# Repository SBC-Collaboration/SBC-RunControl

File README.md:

#  SBC-RunControl

Data acquisition software for the Scintillating Bubble Chamber experiment. For more details, please use the documentation linked below.

## [Documentation](https://runcontrol.readthedocs.io)
- [Usage](https://runcontrol.readthedocs.io/stable/usage.html)
- [Project Description](https://runcontrol.readthedocs.io/stable/project_description.html)
- [Data Formats](https://runcontrol.readthedocs.io/stable/data_format.html)
- [Documentation](https://runcontrol.readthedocs.io/stable/documentation.html)
- [Git workflow and guidelines](https://runcontrol.readthedocs.io/stable/git_workflow.html)
- [API](https://runcontrol.readthedocs.io/stable/api.html)
- [Changelog](https://runcontrol.readthedocs.io/stable/changelog.html)

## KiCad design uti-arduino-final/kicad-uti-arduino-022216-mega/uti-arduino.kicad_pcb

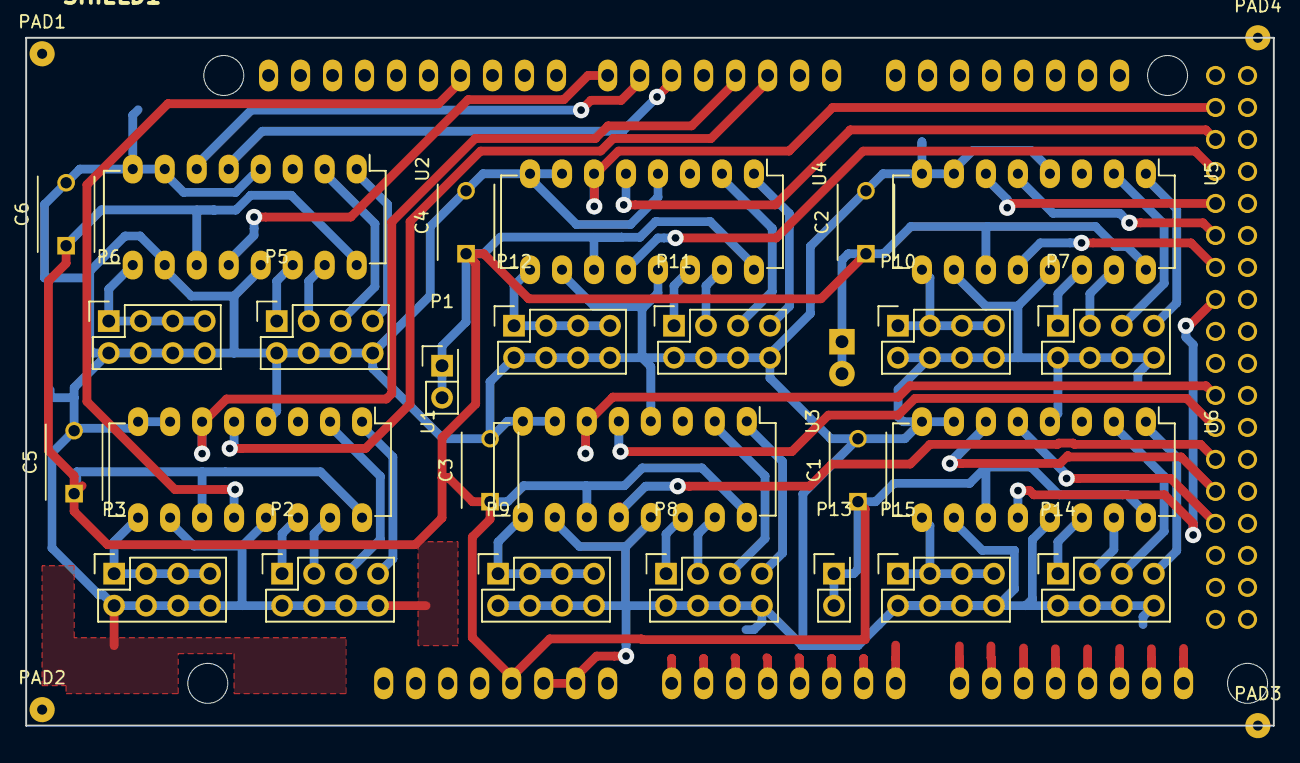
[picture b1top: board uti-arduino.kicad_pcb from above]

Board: 2 copper layers, 99.1 x 54.6 mm, 32 parts (1 on the bottom side), 50 nets.

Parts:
C1, C2, C3, C4, C5, C6: 100n; C_Disc_D6_P5
P1, P13: CONN_01X02; Socket_Strip_Straight_2x01
P2, P3, P5, P6, P7, P8, P9, P10, P11, P12, P14, P15: CONN_02X04; Socket_Strip_Straight_2x04
P4: CONN_01X02; Socket_Strip_Straight_1x02
PAD1: Pad1; SolderWirePad_single_0-8mmDrill
PAD2: Pad2; SolderWirePad_single_0-8mmDrill
PAD3: Pad3; SolderWirePad_single_0-8mmDrill
PAD4: Pad4; SolderWirePad_single_0-8mmDrill
SHIELD1: ARDUINO_SHIELD; ARDUINO_MEGA_SHIELD
U1, U2, U3, U4, U5, U6: UTI; DIP-16_W7.62mm_LongPads

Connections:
+5V: C1.1, C2.1, C3.1, C4.1, C5.1, C6.1, P1.1, P1.2, P4.1, P4.2, P13.1, P13.2, SHIELD1.5V, U1.11, U1.16, U2.11, U2.16, U3.11, U3.16, U4.11, U4.16, U5.11, U5.16, U6.11, U6.16
GND: C1.2, C2.2, C3.2, C4.2, C5.2, C6.2, P2.2, P2.4, P2.6, P2.8, P3.2, P3.4, P3.6, P3.8, P5.2, P5.4, P5.6, P5.8, P6.2, P6.4, P6.6, P6.8, P7.2, P7.4, P7.6, P7.8, P8.2, P8.4, P8.6, P8.8, P9.2, P9.4, P9.6, P9.8, P10.2, P10.4, P10.6, P10.8, P11.2, P11.4, P11.6, P11.8, P12.2, P12.4, P12.6, P12.8, P14.2, P14.4, P14.6, P14.8, P15.2, P15.4, P15.6, P15.8, SHIELD1.GND1, SHIELD1.GND2, U1.4, U1.7, U1.8, U1.10, U1.13, U2.4, U2.7, U2.8, U2.10, U2.13, U3.4, U3.7, U3.8, U3.10, U3.13, U4.4, U4.7, U4.8, U4.10, U4.13, U5.4, U5.7, U5.8, U5.10, U5.13, U6.4, U6.7, U6.8, U6.10, U6.13
unnamed: P2.1, U1.14
unnamed: P2.3, U1.15
unnamed: P2.5, U1.2
unnamed: P2.7, U1.1
unnamed: P3.1, P3.3, P3.5, P3.7, U1.9
unnamed: P5.1, U2.14
unnamed: P5.3, U2.15
unnamed: P5.5, U2.2
unnamed: P5.7, U2.1
unnamed: P6.1, P6.3, P6.5, P6.7, U2.9
unnamed: P7.1, U5.14
unnamed: P7.3, U5.15
unnamed: P7.5, U5.2
unnamed: P7.7, U5.1
unnamed: P8.1, U3.14
unnamed: P8.3, U3.15
unnamed: P8.5, U3.2
unnamed: P8.7, U3.1
unnamed: P9.1, P9.3, P9.5, P9.7, U3.9
unnamed: P10.1, P10.3, P10.5, P10.7, U5.9
unnamed: P11.1, U4.14
unnamed: P11.3, U4.15
unnamed: P11.5, U4.2
unnamed: P11.7, U4.1
unnamed: P12.1, P12.3, P12.5, P12.7, U4.9
unnamed: P14.1, U6.14
unnamed: P14.3, U6.15
unnamed: P14.5, U6.2
unnamed: P14.7, U6.1
unnamed: P15.1, P15.3, P15.5, P15.7, U6.9
unnamed: SHIELD1.2, U1.5
unnamed: SHIELD1.3, U1.6
unnamed: SHIELD1.5, U2.5
unnamed: SHIELD1.6, U2.6
unnamed: SHIELD1.7, U2.12
unnamed: SHIELD1.11, U1.12
unnamed: SHIELD1.22, U4.6
unnamed: SHIELD1.24, U4.5
unnamed: SHIELD1.26, U4.12
unnamed: SHIELD1.28, U5.6
unnamed: SHIELD1.30, U5.5
unnamed: SHIELD1.32, U5.12
unnamed: SHIELD1.34, U6.12
unnamed: SHIELD1.40, U3.6
unnamed: SHIELD1.42, U3.5
unnamed: SHIELD1.44, U3.12
unnamed: SHIELD1.46, U6.6
unnamed: SHIELD1.48, U6.5

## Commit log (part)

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2025-02-11 Add a new CAEN page. Add more configs
2025-02-11 Change config module to match settings page
2025-02-12 Add CAEN group range setting
2025-02-12 Change some of the config and UI code to work with UI changes
2025-02-12 Save CAEN data dicts in a list and write at the end
2025-02-12 Add trigger counting mode box
2025-02-13 Move RedDigitizerPlusPlus install from local to pip
2025-02-14 Change some variable names to match CAEN driver and UI
2025-02-17 Use enabled channels and record length from CAEN to set writer, since rec_length can only be multiples of 3
2025-02-18 Remove json wave names to reduce length, also print gates in Arduino serial
2025-02-18 reset niusb device at starting run
2025-02-18 Stop saving wave name in clock arduino json
2025-02-18 Revert to default tab
2025-02-20 Update CAEN plot on main page
2025-02-20 Change event info binary file to have string as trigger source
2025-02-20 Make clock arduino run faster With LED gate and all 16 channels, now the clock arduino can complete a loop in 100us. Changes made include: 1. Simplify the logic for checking time at the end 2. Only m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
2025-02-24 Add CAEN enable in config, change number of modules that need to be ready at each stage
2025-02-24 Add loop time in arduino json
2025-02-24 Minor changes
2025-02-25 Add enable field for acoustics module
2025-02-25 Now acoustics module can be disabled, and also writes the ini file
2025-02-25 Edit more of the buddies in Pyside6 designer
2025-02-26 Rename seg count boxes
2025-02-26 Implement acousitcs settings in config module
2025-02-26 Fix acoustics ini file generation to match GaGe's requirements
2025-02-26 Remove acoustics channel enable checkbox
2025-02-27 Clean up unused imports
2025-03-04 Change unit of acoustics dc offset
2025-03-04 RC now saves acoustic channel DC offset in .ini file
2025-03-04 Add acous channel name saving/loading
2025-03-05 Deal with case when wave is wrapped, i.e. (duty+phase)>period. Also remove state to make it faster. A loop completes in ~60us now.
2025-03-05 Set LED inhibit pin on trigger arduino to be output. Otherwise it'll always be high
2025-03-05 Add sipm amp3 status light
2025-03-09 Consolidate project structure into project description, also update configuration file definition
2025-03-09 Add definition for CAEN and GaGe data
2025-03-09 Update project structure, and chapter hierachy
2025-03-10 Update dependencies docs
2025-03-10 Move info from main README to docs
2025-03-11 Update API page of ducmentation
2025-03-28 Move signal definitions to MainWindow class
2025-03-28 Move signal declaration to class level
2025-03-28 Write documentation for some modules, also remove unused code in config module
2025-04-18 Add back a line removed by mistake
2025-04-24 Add documentation on sphinx
2025-04-25 Add name field to CAEN config to tell which SiPM amp channel is connected
2025-04-25 Load combo box model when loading UI
2025-04-25 Demote all combobox to normal combobox widgets
2025-04-30 Add GaGe driver as git submodule dependency
2025-05-01 Update GaGe driver to allow running script as root
2025-05-01 Update init scripts. It installs to system path and adds itself to sudoer for nopasswd execution. Now only the first time needs password, and then driver install doesn't require password.
2025-05-02 Add some tutorial on git submodule
2025-05-02 remove NIUSB subtree dependency
2025-05-02 Add arduino sketches as submodule repo
2025-05-06 Add git submodule update commands in init script
2025-05-12 Changes to acoustics driver. Compile .so shared library in makefile
2025-05-12 Change import for niusb library
2025-05-20 Init script will now copy root script when it's updated. Also add current user to respective groups for permission
2025-05-20 Change log and data path with relative path
2025-05-20 Change signals from modules to show {module}-disabled
2025-05-20 Change the structure of config file
2025-05-21 Update and add some mutex locks for syncing between threads
2025-05-21 separate SQL query and values to make it safer.
2025-05-21 Add section to init script to save SQL token to file, and load it up
2025-05-21 Add event pressure profile display on main window
2025-05-21 Add PLC Modbus variables in settings window
2025-05-21 Config class can read and write PLC modbus register settings
2025-05-21 Update entries of the master config file
2025-05-22 Update data format and dependencies documentation.
2025-05-22 Change range allowed for pressure display
2025-05-29 Simplify rc log file name
2025-05-29 Add lock file to ensure only one instance of run control is running on a machine.
2025-05-29 Fix NIUSB DIO error, and change pin name after rewiring in DIO box.
2025-05-30 Add run exit code to SQL run database.
2025-05-30 Fix mutex checks for camera config. Flag set at run start is only reset at run end, not event end.
2025-06-02 modbus changes
2025-06-02 modbus and rc changes
2025-06-02 Change helper functions into private methods of the class
2025-06-02 More changes to make helper functions work as methods
2025-06-03 Simplify general enabled boxes
2025-06-03 Minor changes and bug fixes for modbus class.
2025-06-03 Some more minor changes
2025-06-03 Add UI logic for PLC pressure cycle timeout, also fix bugs.
2025-06-04 Create a symlink to current run directory in addition to current event.
2025-06-04 Start populating run_info and event_info binary metadata files.
2025-06-04 Use logger instead of print statement for some logs.
2025-06-04 Create error signal for all modules.
2025-06-04 Update writer and the documentation of data headers.
2025-06-05 Updated to add plc data writing to log files
2025-06-06 Update SiPM and CAEN channel names now that they are plugged in.
2025-06-06 Update SQL to use password file directly. Also parameterize SMB command.
2025-06-07 Minor changes to UI.
2025-06-07 Update init script to handle smb token.
2025-06-07 Update event pressure
2025-06-07 Update sources list
2025-06-07 Implement error status in the status light.
2025-06-08 Implement autorun.
2025-06-09 Rearrange UI, remove some enable buttons, and add some. Implement disabling writer.
2025-06-10 Minor changes in sha256sum check.
2025-06-11 updating SBCABort for new output file format
2025-06-11 Update gati-linux-driver to use ssh link for submodule
2025-06-11 Include run control version in run_info and RUnData SQL.
2025-06-11 Update changelog title
2025-06-12 test commit
2025-06-13 update to fix cam thread issue
2025-06-13 Add plotting for acoustic waveforms at end of event.
2025-06-13 Update lockfile permission
2025-06-16 changes to save 10s data
2025-06-19 Add a page of documentation on git workflow guidelines.
2025-06-20 Reference config paths relative to main RC directory, and not CWD. Add acous plotting booleans in settings file.
2025-06-20 Add LED control voltage in PLC modbus section.
2025-06-27 Implement writing LED control voltage to PLC modbus registers
2025-07-01 Fix CAEN seg fault and error when running external or self triggers.
2025-07-01 Consolidate CAEN plots into subplots
2025-07-02 Plot CAEN waveforms in subplots and add legends on the side.
2025-07-03 Update changelog.
2025-07-07 Miscellaneous acous plotter fixes
2025-07-07 Prepare for release v0.2.1
2025-07-07 Use git tags for run control version number retrieval
2025-07-08 Correct the number of events field in SQL RunData table.
2025-07-09 Position arduino modules now disables UTI chip at start of run, and enables them back at end of run.
2025-07-09 Add Arduino manual upload sketch button
2025-07-10 Fix LED control in PLC module.
2025-07-10 Move config file to ~/.config/runcontrol/config.json
2025-07-10 Define error codes in guardian module. Start switch case in the function.
2025-07-11 Read HV, QP ADC, and per-channel DAC offset.
2025-07-14 Write SiPM voltages to file. Move bias/unbias to start/stop event, and connect/disconnect amps at start/stop run.
2025-07-14 Remove config_path from settings
2025-07-15 changes to add Pre and post trig time, waveform to waveforms in binary file
2025-07-15 Change Waveform to Waveforms in binary file
2025-07-15 Update the settings window to save pre and post trigger len for acous workaround trigger. Update codumentaion and bugfixes.
2025-07-15 Add pre trigger and post trigger boxes for acous. Rename depth and seg size to use original names
2025-07-15 For NIUSB module, try freeing the USB device is resource is busy.
2025-07-16 Keep init script in original path. Reorder changelog
2025-07-16 Use QProcess instead of multiprocessing for running acous driver. This way we can do error handling and signaling based on stdout and stderr
2025-07-17 Fixed the bug that SiPM are not biased at start of event. Added a line waiting for command execution to finish.
2025-07-18 Update docstring for SiPM Amp class.
2025-07-18 Prepare for v0.3.1
2025-07-23 Update documentation for API and readthedocs
2025-07-31 Move git subtree documentation
2025-07-31 Adding new Slack messaging code
2025-07-31 Add new python packages for slack messaging
2025-08-01 Update error messaging code to use SBCAlarm slack app
2025-08-14 Fix error code names
2025-08-14 Remove unused dependencies
2025-08-18 Add a checkbox for enabling slack alarms. Also update docs
2025-08-18 Move slack channel ID to settings page. More error catching
2025-08-20 Now modbus module will wait for NIUSB to detect camera has finished an event before turning off LED control voltages. Also now the LED checkboxes work in enabling the control voltage settings.
2025-08-20 Prepare for v0.3.3
2025-08-22 Add a gain setting for arducams
2025-09-12 Convert some more error logging to signal to guardian module.
2025-10-08 Better handling for camera time lapse handout
2025-10-08 Move jar position sensor enable/disable to start/stop of event, not runs. Add a checkbox to toggle it on/off.
2025-10-08 Add a button for running SiPM IV curves.
2025-10-09 Add more options for sources and locations
2025-10-09 Change stop run button to be checked when pressed, not disabled. So it can be unchecked if need to continue run
2025-10-09 Prepare for v0.4.0
2025-10-16 improve SiPM bias procedure
2025-11-03 Changes to UI and modules to add LED out PRE/POST and pressure cycle ramp1/rampdown/rampup settings in the PLC. TODO: Update SQL columns while updating the sql module here.
2025-11-03 Minor bug fix for CAEN module.
2025-11-04 Minor fix in acoustic driver
2025-11-04 Fix acoustic driver filename problem
2025-11-04 Update SQL table.
2025-11-05 Add digiscope status light
2025-11-05 Add digiscope config into settings window.
2025-11-05 Update digiscope.py
    work in progress
2025-11-05 Add a timeout for GaGe driver at the end of event.
2025-11-05 Add version display
2025-11-06 If SiPM voltage readbacks fail, redo instead of send error messages.
2025-11-06 Add digiscope to list modules that RC will expect to send a signal.
2025-11-06 Minor change to how SiPM biasing fails
2025-11-06 Prepare for v0.4.4
2025-11-06 Save SiPM bias offset as class variable.
2025-11-06 Clean up arduino sketch force upload button command
2025-11-06 Rename Modbus module to PLC
2025-11-07 Fix checked status of stop run button in a new run. Update docs
2025-11-07 bugfix.
2025-11-07 Clean up module names and log messages
2025-11-08 Add a timeout for camera at the end of events.
2025-11-10 Include more information in error messages.
2025-11-10 Include module name in logger messages.
2025-11-12 Bugfix for guardian
2025-11-12 Add error handling for camera freezing at start of event.
2025-11-12 Include real time display of current argon pressure
2025-11-14 Link autorun, source config from main window to settings window.
2025-11-14 Make stop run button available if clicked at starting_event
2025-11-14 Prepare for v0.4.6
2025-11-14 Better handling of camera status after error, and make sure GaGe process is closed before starting a new one.
2026-01-11 Minor fix in digiscope code to fix deprecated numpy usage
2026-01-11 Fix of camera logic to hopefully reboot camera if encounters an error
2026-01-11 Prepare for v0.4.7
2026-01-23 Update documentation to include digiscope and recon data.
2026-02-06 Add in a wait module to make sure event_stop state last at least a certain time.
2026-02-18 Add box to set end-of-event wait time
2026-02-23 Update recon doc to include bubble finder
2026-04-17 Update recon_data_format.md
    3D Reconstruction
